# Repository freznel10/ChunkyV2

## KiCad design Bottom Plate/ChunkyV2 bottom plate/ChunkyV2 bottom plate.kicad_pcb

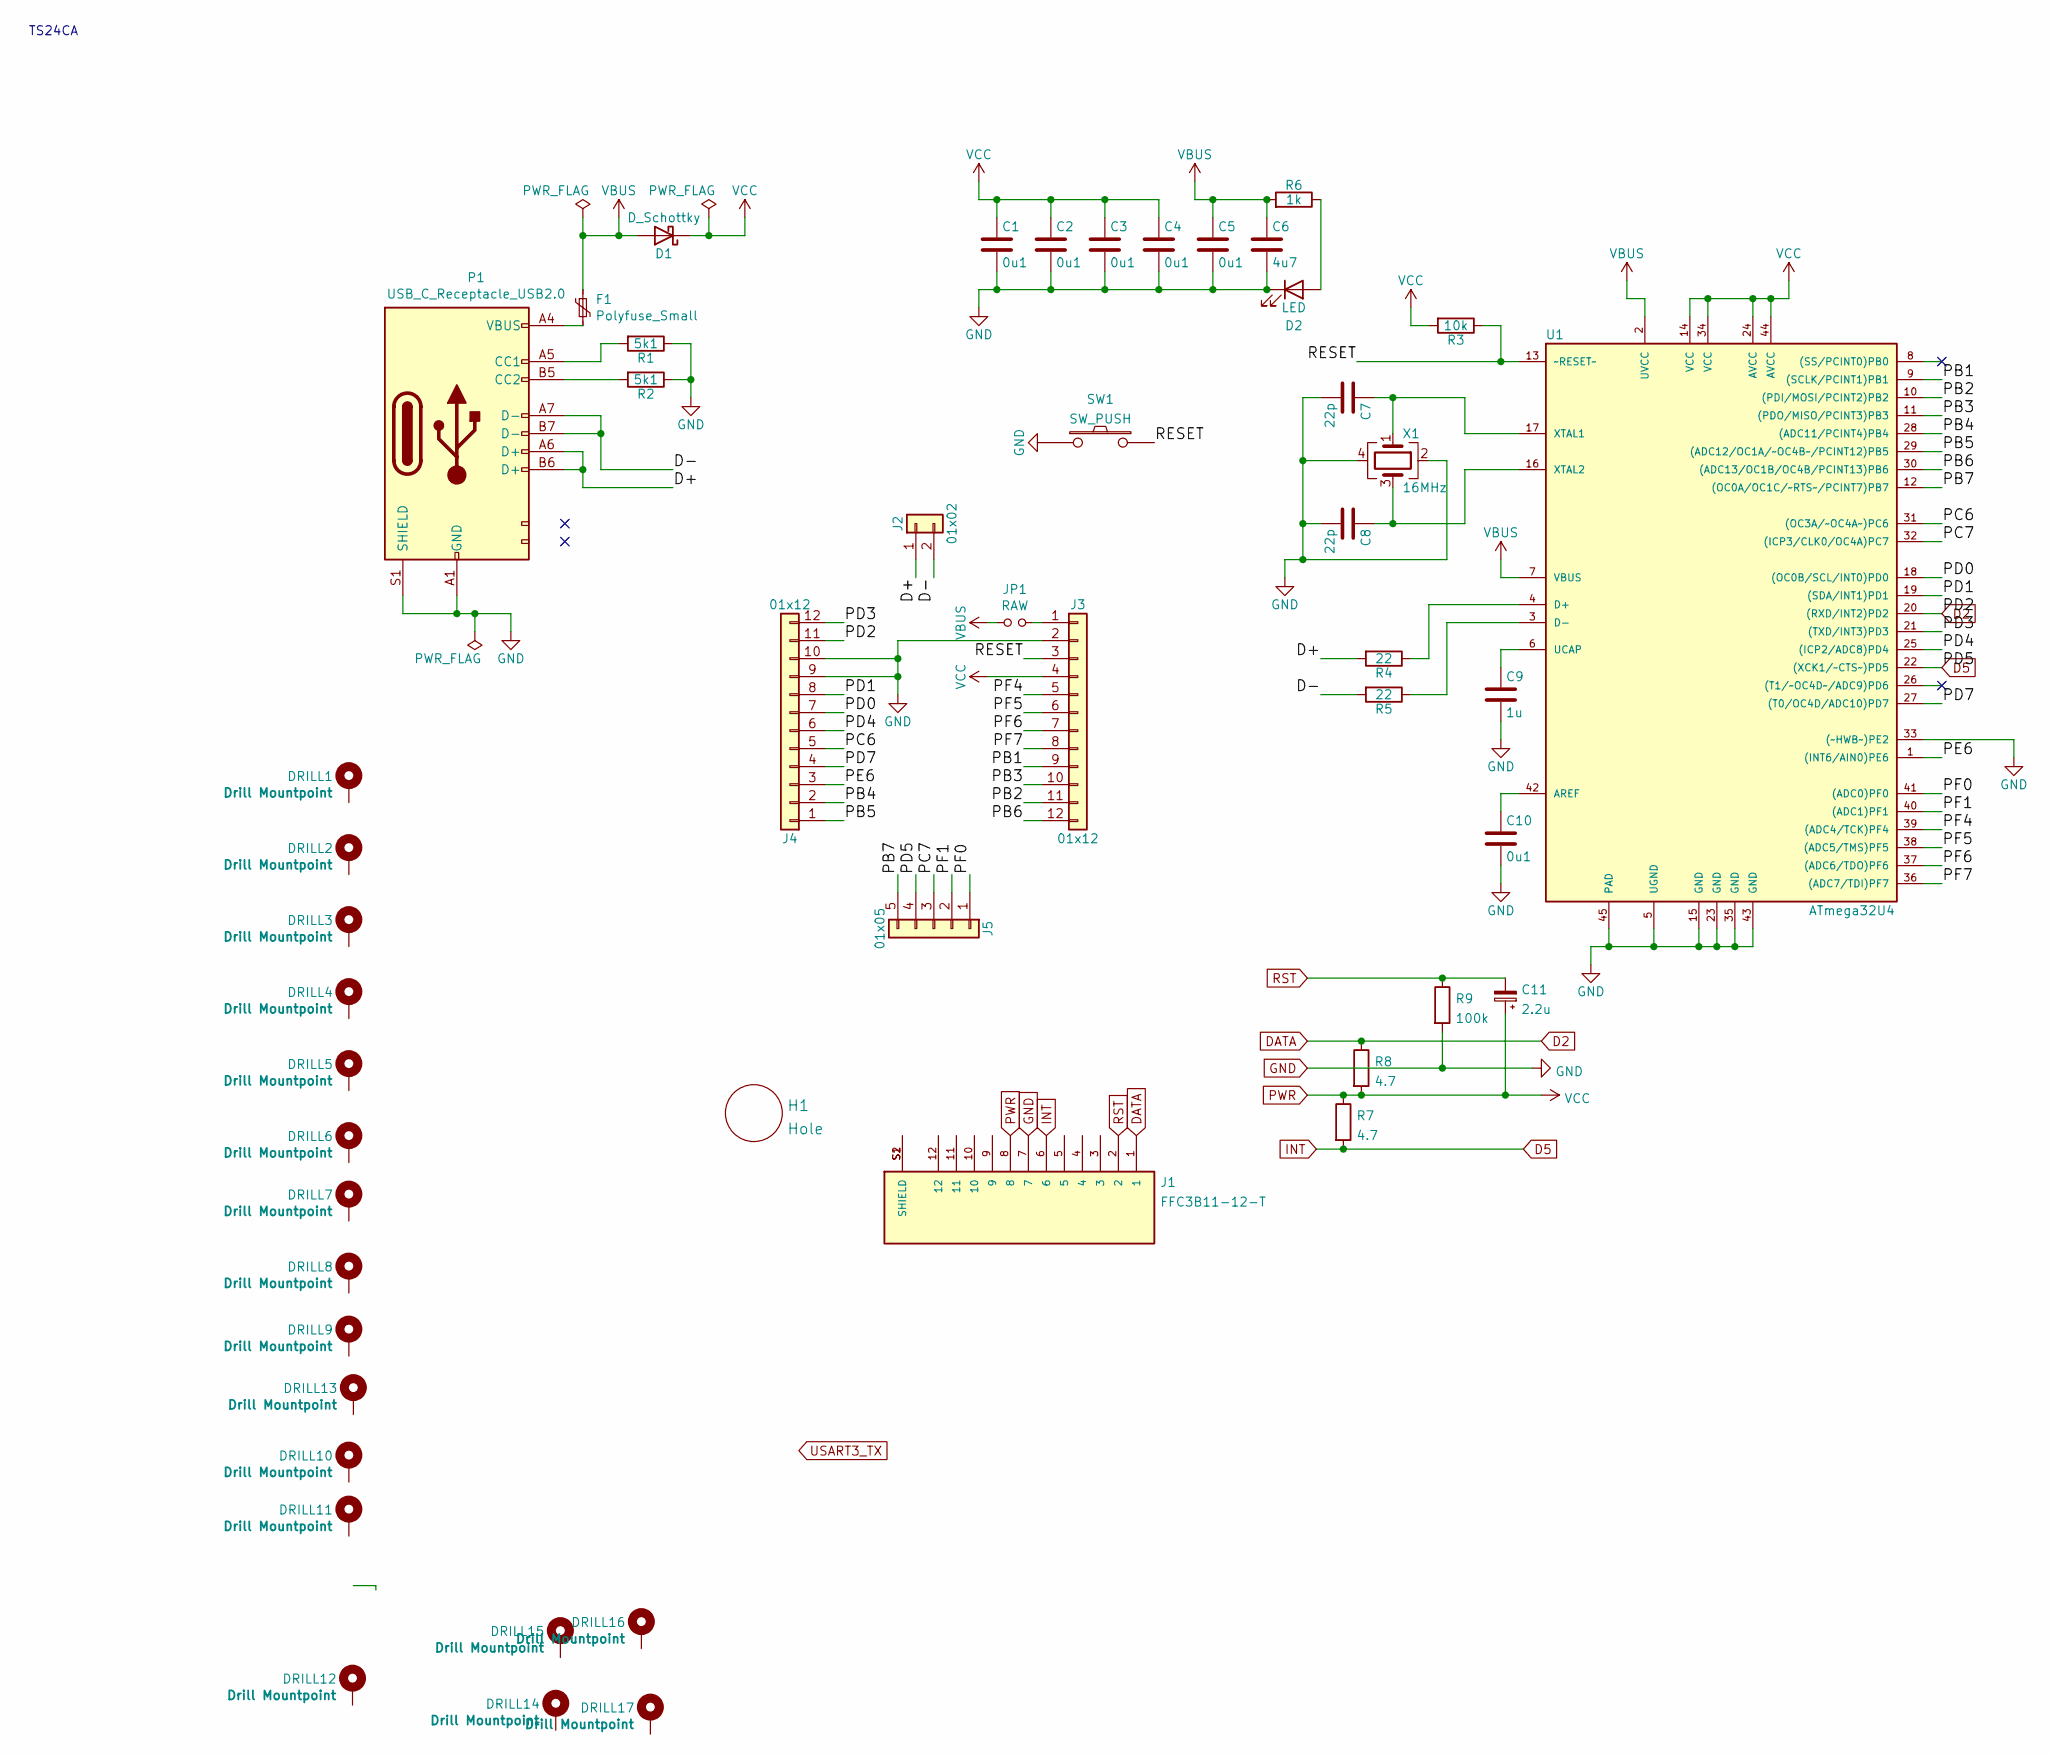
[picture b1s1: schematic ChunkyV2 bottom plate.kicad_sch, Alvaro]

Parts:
C1, C2, C3, C4, C5, C10: 0u1; C_0603_1608Metric; LCSC C83054
C6: 4u7; C_0603_1608Metric; LCSC C69182
C7, C8: 22p; C_0603_1608Metric; LCSC C107451
C9: 1u; C_0603_1608Metric; LCSC C83059
C11: 2.2u; C_0805_2012Metric_Pad1.18x1.45mm_HandSolder; LCSC C49217
D1: D_Schottky; D_SOD-123; LCSC C2920035
D2: LED; LED_0603_1608Metric; LCSC C138547
DRILL1, DRILL2, DRILL4, DRILL10, DRILL11, DRILL14, DRILL15, DRILL16, DRILL17: Drill Mountpoint; MountingHole_3.2mm_M3_Pad_Via
DRILL3, DRILL5, DRILL6, DRILL7, DRILL8, DRILL9, DRILL12, DRILL13: Drill Mountpoint; MountingHole_2.2mm_M2_DIN965_Pad
F1: Polyfuse_Small; Fuse_1206_3216Metric; LCSC C99561
H1: Hole; SK8707
J1: FFC3B11-12-T; GCT_FFC3B11-12-T; PARTREV A
J2: 01x02; Pins2
J3, J4: 01x12; Pins12
J5: 01x05; Pins5
JP1: RAW; SolderJumper-2_P1.3mm_Open_Pad1.0x1.5mm
P1: USB_C_Receptacle_USB2.0; USB-C-C168688; LCSC C168688
R1, R2: 5k1; R_0603_1608Metric; LCSC C328432
R3: 10k; R_0603_1608Metric; LCSC C269701
R4, R5: 22; R_0603_1608Metric; LCSC C325646
R6: 1k; R_0603_1608Metric; LCSC C394536
R7: 4.7; R_0805_2012Metric_Pad1.20x1.40mm_HandSolder
R8: 4.7; R_0805_2012Metric_Pad1.20x1.40mm_HandSolder; LCSC C17673
R9: 100k; R_0805_2012Metric_Pad1.20x1.40mm_HandSolder; LCSC C478884
SW1: SW_PUSH; SMD_Tacticle_Switch_TS24CA_flipable
U1: ATmega32U4; QFN-44-1EP_7x7mm_P0.5mm_EP5.2x5.2mm; LCSC C45874
X1: 16MHz; Crystal_SMD_SeikoEpson_FA238-4Pin_3.2x2.5mm; LCSC C70562

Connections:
/D+: J2.1, P1.A6 (D+), P1.B6 (D+), R4.2
/D-: J2.2, P1.A7 (D-), P1.B7 (D-), R5.2
/PB1: J3.9, U1.9 ((SCLK/PCINT1)PB1)
/PB2: J3.11, U1.10 ((PDI/MOSI/PCINT2)PB2)
/PB3: J3.10, U1.11 ((PDO/MISO/PCINT3)PB3)
/PB4: J4.2, U1.28 ((ADC11/PCINT4)PB4)
/PB5: J4.1, U1.29 ((ADC12/OC1A/~OC4B~/PCINT12)PB5)
/PB6: J3.12, U1.30 ((ADC13/OC1B/OC4B/PCINT13)PB6)
/PB7: J5.5, U1.12 ((OC0A/OC1C/~RTS~/PCINT7)PB7)
/PC6: J4.5, U1.31 ((OC3A/~OC4A~)PC6)
/PC7: J5.3, U1.32 ((ICP3/CLK0/OC4A)PC7)
/PD0: J4.7, U1.18 ((OC0B/SCL/INT0)PD0)
/PD1: J4.8, U1.19 ((SDA/INT1)PD1)
/PD3: J4.12, U1.21 ((TXD/INT3)PD3)
/PD4: J4.6, U1.25 ((ICP2/ADC8)PD4)
/PD7: J4.4, U1.27 ((T0/OC4D/ADC10)PD7)
/PE6: J4.3, U1.1 ((INT6/AIN0)PE6)
/PF0: J5.1, U1.41 ((ADC0)PF0)
/PF1: J5.2, U1.40 ((ADC1)PF1)
/PF4: J3.5, U1.39 ((ADC4/TCK)PF4)
/PF5: J3.6, U1.38 ((ADC5/TMS)PF5)
/PF6: J3.7, U1.37 ((ADC6/TDO)PF6)
/PF7: J3.8, U1.36 ((ADC7/TDI)PF7)
/RESET: J3.3, R3.1, SW1.2, U1.13 (~RESET~)
D2: J1.1, J4.11, R8.1, U1.20 ((RXD/INT2)PD2)
D5: J1.6, J5.4, R7.2, U1.22 ((XCK1/~CTS~)PD5)
GND: C1.2, C2.2, C3.2, C4.2, C5.2, C6.2, C7.2, C8.2, C9.2, C10.2, D2.1 (K), J1.7, J3.2, J4.9, J4.10, P1.A1 (GND), P1.B1 (GND), P1.S1 (SHIELD), R1.1, R2.1, R9.2, SW1.1, U1.5 (UGND), U1.15 (GND), U1.23 (GND), U1.33 ((~HWB~)PE2), U1.35 (GND), U1.43 (GND), U1.45 (PAD), X1.2, X1.4
unnamed: C7.1, U1.17 (XTAL1), X1.1
unnamed: C8.1, U1.16 (XTAL2), X1.3
unnamed: C9.1, U1.6 (UCAP)
unnamed: C10.1, U1.42 (AREF)
unnamed: D2.2 (A), R6.1
unnamed: F1.2, P1.A4 (VBUS), P1.B4 (VBUS)
unnamed: J1.S1 (SHIELD), J1.S2 (SHIELD)
unnamed: J3.1, JP1.2
unnamed: P1.A5 (CC1), R1.2
unnamed: P1.B5 (CC2), R2.2
unnamed: R4.1, U1.4 (D+)
unnamed: R5.1, U1.3 (D-)
PWR: C1.1, C2.1, C3.1, C4.1, C11.1, D1.1 (K), J1.8, J3.4, R3.2, R7.1, R8.2, U1.14 (VCC), U1.24 (AVCC), U1.34 (VCC), U1.44 (AVCC)
RST: C11.2, J1.2, R9.1
VBUS: C5.1, C6.1, D1.2 (A), F1.1, JP1.1, R6.2, U1.2 (UVCC), U1.7 (VBUS)

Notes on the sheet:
TS24CA

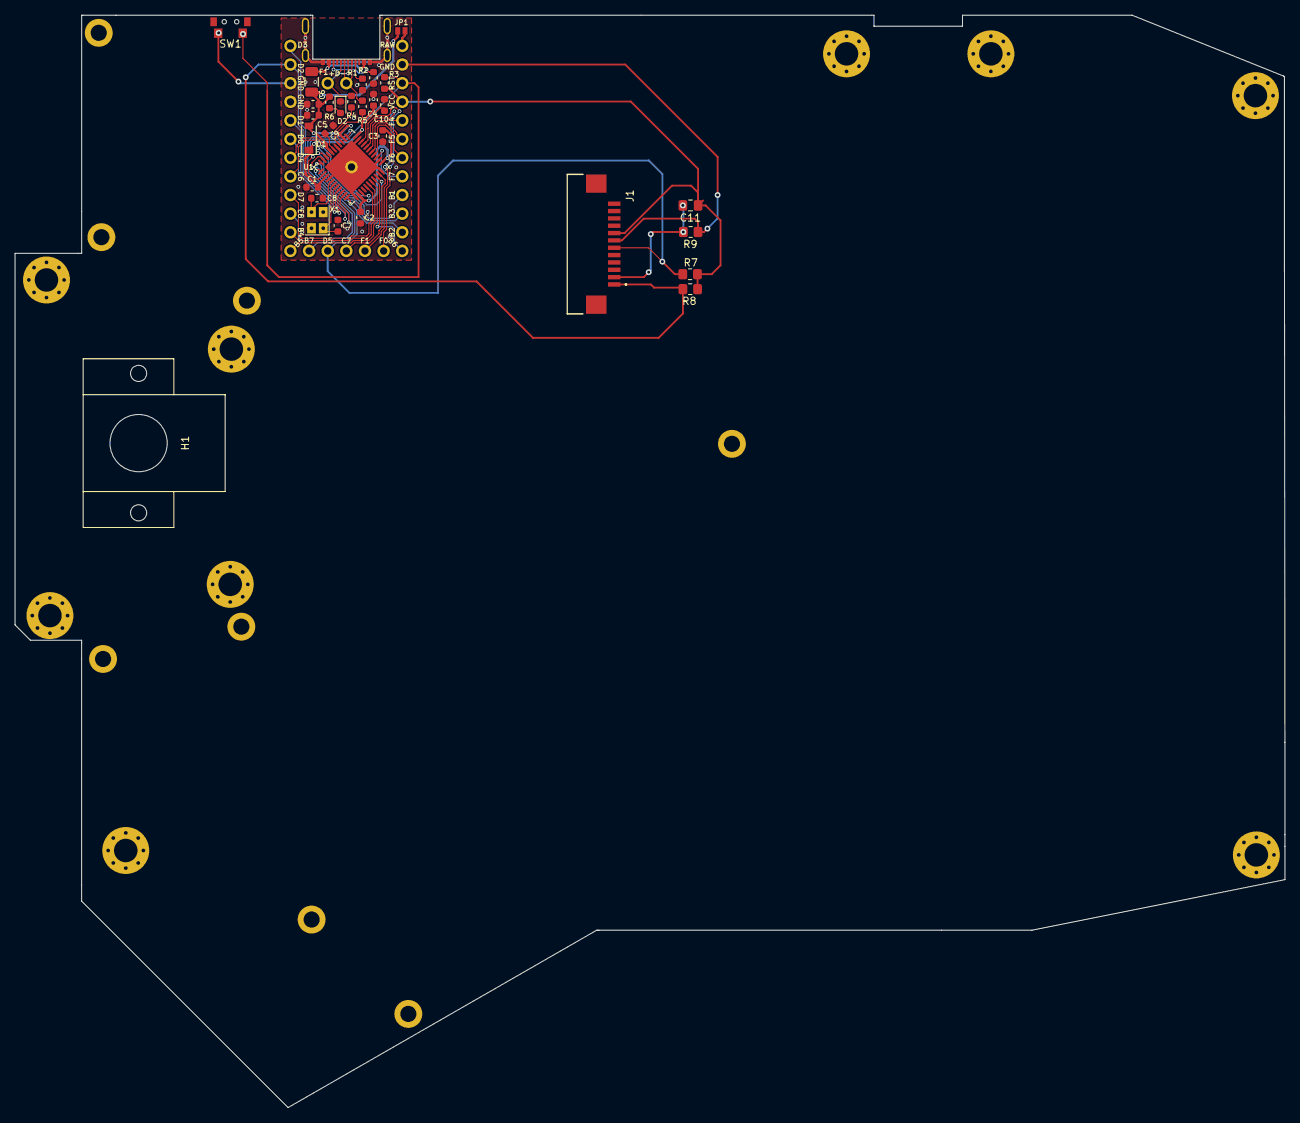
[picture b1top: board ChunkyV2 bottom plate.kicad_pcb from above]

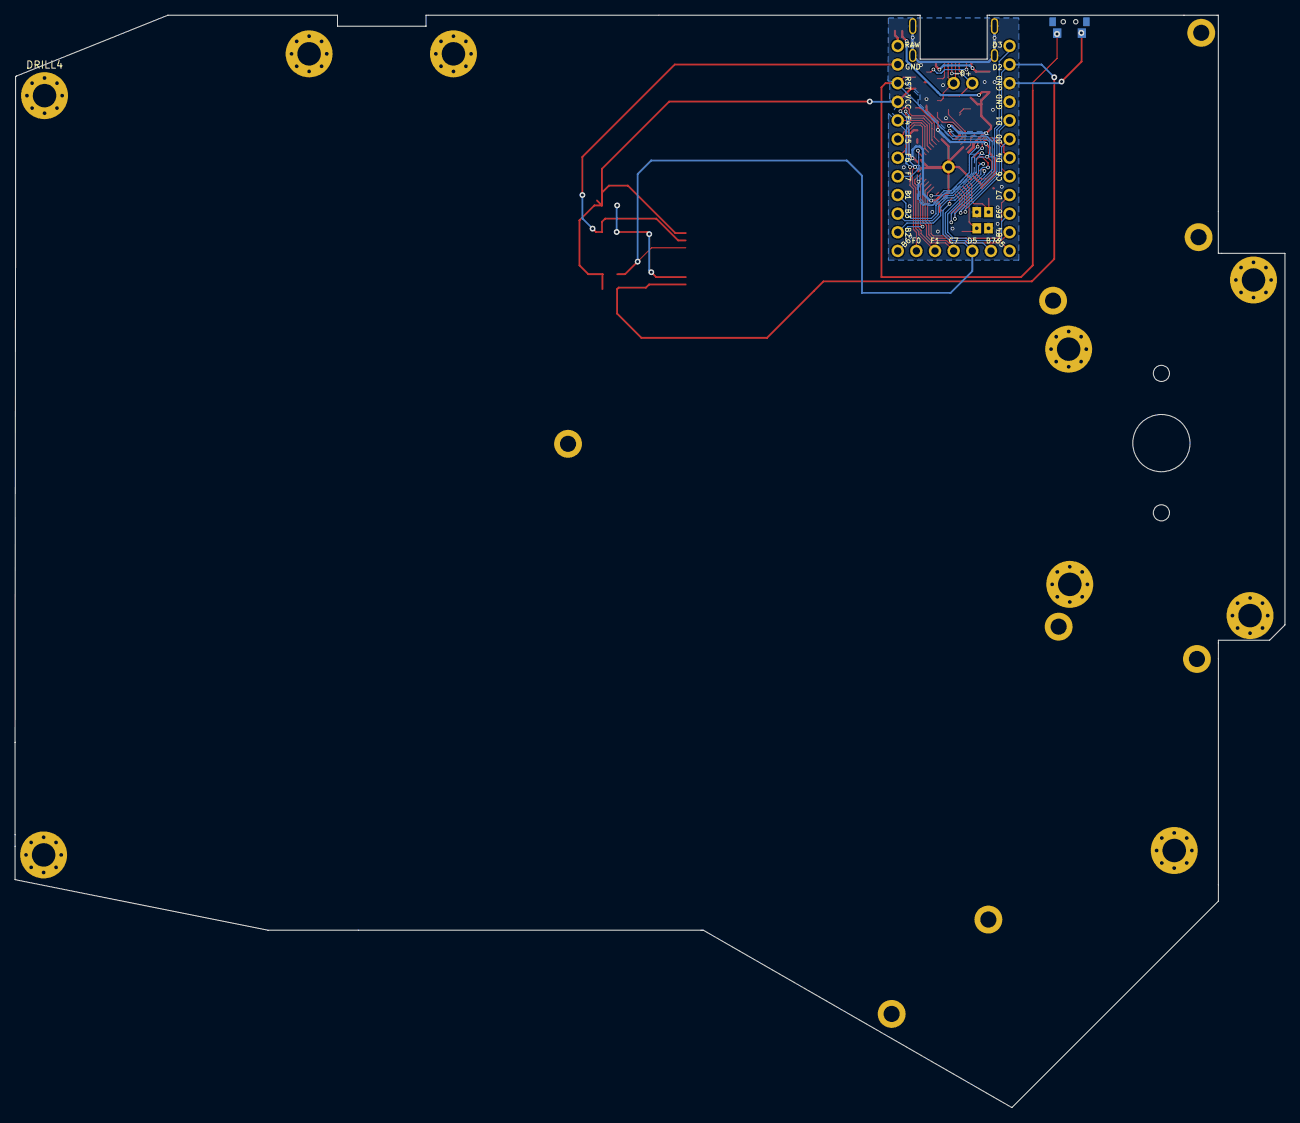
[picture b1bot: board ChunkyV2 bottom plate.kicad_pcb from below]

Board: 2 copper layers, 173.1 x 148.9 mm, 51 parts (12 on the bottom side), 42 nets.

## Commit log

2022-01-20 Additional files
